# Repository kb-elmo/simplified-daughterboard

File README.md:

# Simplified USB-C Daughterboard

[![CC BY-SA 4.0][cc-by-sa-shield]][cc-by-sa] [![Open Source Love][os-love]](https://opensource.com/resources/what-open-hardware)

This daughterboard features minimal electronics required for breaking out the VBUS, data and ground lines from a USB type C port.  
It includes a basic USB shielding circuit but has no ESD protection or fuse built in.

Fuse and (optional) ESD protection should be added on the main PCB if you want to use this for your project.

The daughterboard is pinout and size compatible with the [Unified Daughterboard by ai03](https://github.com/ai03-2725/Unified-Daughterboard).

Since the single PCB alone is too small for SMT assembly from JLCPCB and automatic panel assembly is currently not possible with them I created a 2x2 panelized version that works with JLCPCB assembly. You can find it in the fab files (linked below).

---

[Panelized PCB](fab/sDB_panel.kicad_pcb)

[Gerbers](fab/gerbers.zip)

[LCSC BOM](fab/bom.csv)

[JLC CPL](fab/pos.csv)

[USB connector](https://lcsc.com/product-detail/USB-Type-C_Korean-Hroparts-Elec-TYPE-C-31-M-12_C165948.html)

[JST connector](https://www.digikey.com/product-detail/en/jst-sales-america-inc/SM04B-SRSS-TB-LF-SN/455-1804-1-ND/926875)

---

This work is licensed under a
[Creative Commons Attribution-ShareAlike 4.0 International License][cc-by-sa].

[![CC BY-SA 4.0][cc-by-sa-image]][cc-by-sa]

[cc-by-sa]: http://creativecommons.org/licenses/by-sa/4.0/
[cc-by-sa-image]: https://licensebuttons.net/l/by-sa/4.0/88x31.png
[cc-by-sa-shield]: https://img.shields.io/badge/License-CC%20BY--SA%204.0-lightgrey.svg
[os-love]: https://badges.frapsoft.com/os/v2/open-source.png?v=103

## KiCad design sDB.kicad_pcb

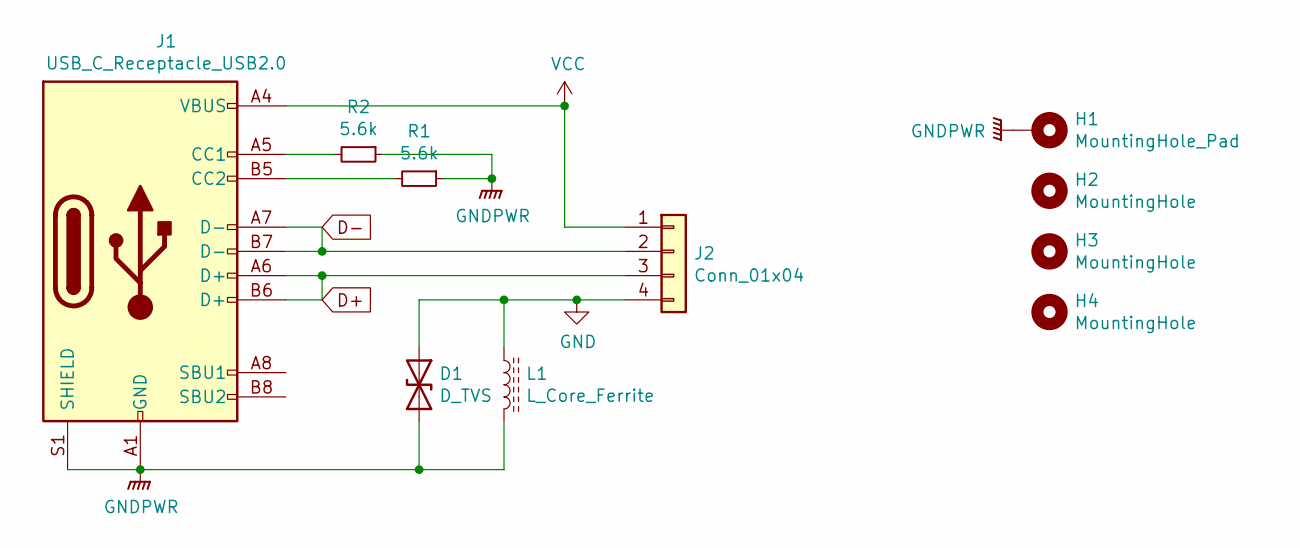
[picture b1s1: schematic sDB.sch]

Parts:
D1: D_TVS; D_SOD-323; LCSC C151996
H1: MountingHole_Pad; Generic-Mounthole-dual
H2, H3, H4: MountingHole; Generic-Mounthole
J1: USB_C_Receptacle_USB2.0; USB_C_Receptacle_HRO_TYPE-C-31-M-12; LCSC C165948
J2: Conn_01x04; JST_SH_SM04B-SRSS-TB_1x04-1MP_P1.00mm_Horizontal
L1: L_Core_Ferrite; L_1206_3216Metric; LCSC C33600
R1, R2: 5.6k; R_0603_1608Metric; LCSC C23189

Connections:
D+: J1.A6 (D+), J1.B6 (D+), J2.3
D-: J1.A7 (D-), J1.B7 (D-), J2.2
GND: D1.1 (A1), J2.4, L1.1
GNDPWR: D1.2 (A2), H1.1, J1.A1 (GND), J1.A12 (GND), J1.B1 (GND), J1.B12 (GND), J1.S1 (SHIELD), L1.2, R1.1, R2.1
unnamed: J1.A5 (CC1), R2.2
unnamed: J1.B5 (CC2), R1.2
VCC: J1.A4 (VBUS), J1.A9 (VBUS), J1.B4 (VBUS), J1.B9 (VBUS), J2.1

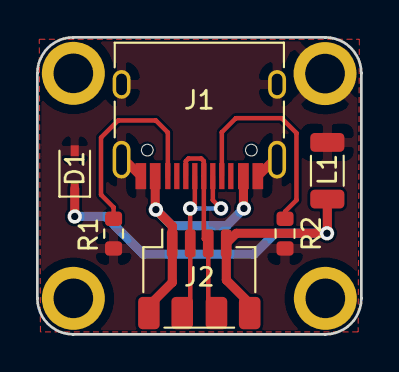
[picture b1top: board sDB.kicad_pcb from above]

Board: 2 copper layers, 18.0 x 16.5 mm, 10 parts (0 on the bottom side), 7 nets.

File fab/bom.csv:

Comment,Designator,Footprint,LCSC
Conn_01x04,J2,custom_parts:JST_SH_SM04B-SRSS-TB_1x04-1MP_P1.00mm_Horizontal,
USB_C_Receptacle_USB2.0,J1,Connector_USB:USB_C_Receptacle_HRO_TYPE-C-31-M-12,C165948
5.6k,"R1,R2",Resistor_SMD:R_0603_1608Metric,C23189
L_Core_Ferrite,L1,Inductor_SMD:L_1206_3216Metric,C33600
D_TVS,D1,Diode_SMD:D_SOD-323,C151996
MountingHole_Pad,H1,custom_parts:Generic-Mounthole-dual,
MountingHole,"H2,H3,H4",custom_parts:Generic-Mounthole,

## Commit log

2021-03-05 fix images
2021-03-05 change image
2021-03-06 Create LICENSE
2021-03-06 update licensing
2021-03-06 remove logo
2021-03-06 add pinout labels
